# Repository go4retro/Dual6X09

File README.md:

# Dual 6X09E Adapter Schematic and Printed Circuit Board
This PCB will allow the use of two different 6X09E variants in a 6809E-based system.  Only one CPU can be active at any time, and the CPU must be selected before boot.

## Technical Details

The Motorola MC6809E and the Hitachi 63C09E microprocessors both support tristating most of their I/O pins as a way to support a multi-processor environment.  The TSC (Tri State Control) line, when high, places most CPU I/O lines in a high impedence (Hi-Z) state, where they can be safely connected to other output lines.  The address, data, and read/write lines are tristated when TSC is set to logical 1 (5volt). Other lines, like E, Q, the various interrupt lines, and RESET are all inputs, which means they can always be connected together.

This is enough to support running two CPUs in a Tandy Color computer.  However, some aftermarket devices that reside in the CPU socket require access to additional output lines on the CPU that are not tri-stated (LIC, AVMA, BUSY, BA, and BS).  These lines tell the rest of the circuit the internal state of the CPU, so it makes sense they are always active.  Thus, these lines must be tri-stated using external components so the relevant signal from the currently active CPU will be sent to the CPU socket. If these signals are not needed, the external circuitry can be simply omitted.

## Purchase
You can purchase this PCB at http://store.go4retro.com/dual-6x09-pcb/

## License
Copyright (C) 2017-20  Jim Brain, RETRO Innovations

These files are free designs; you can redistribute them and/or modify
them under the terms of the Creative Commons Attribution-ShareAlike 
4.0 International License.

You should have received a copy of the license along with this
work. If not, see <http://creativecommons.org/licenses/by-sa/4.0/>.

These files are distributed in the hope that they will be useful,
but WITHOUT ANY WARRANTY; without even the implied warranty of
MERCHANTABILITY or FITNESS FOR A PARTICULAR PURPOSE.  See the
license for more details.

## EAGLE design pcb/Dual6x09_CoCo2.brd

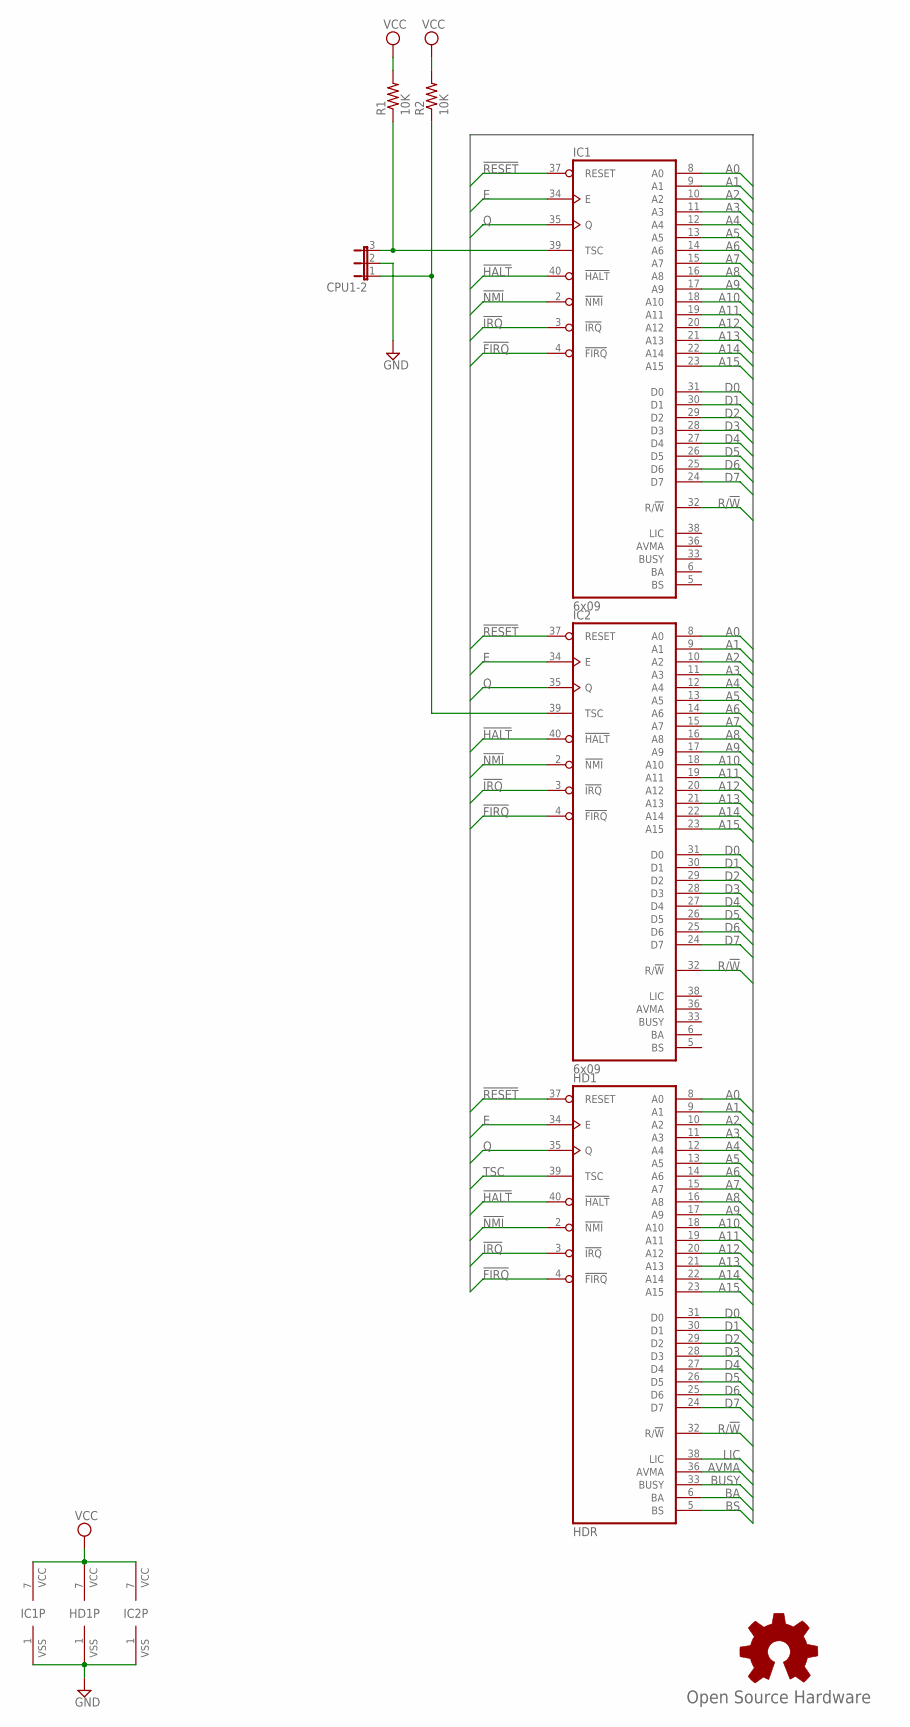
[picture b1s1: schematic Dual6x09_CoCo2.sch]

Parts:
CPU1-2: JP2E; JP2
GOLD_ORB_SM1: Open Source Hardware; OSHW_5MM
HD1: HDR; DIL40-ROUNDPAD
IC1, IC2: 6x09; DIL40-ROUNDPAD
R1, R2: 10K; 0204V

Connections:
!FIRQ: HD1.4 (!FIRQ), IC1.4 (!FIRQ), IC2.4 (!FIRQ)
!HALT: HD1.40 (!HALT), IC1.40 (!HALT), IC2.40 (!HALT)
!IRQ: HD1.3 (!IRQ), IC1.3 (!IRQ), IC2.3 (!IRQ)
!NMI: HD1.2 (!NMI), IC1.2 (!NMI), IC2.2 (!NMI)
!RESET: HD1.37 (RESET), IC1.37 (RESET), IC2.37 (RESET)
A0: HD1.8 (A0), IC1.8 (A0), IC2.8 (A0)
A1: HD1.9 (A1), IC1.9 (A1), IC2.9 (A1)
A2: HD1.10 (A2), IC1.10 (A2), IC2.10 (A2)
A3: HD1.11 (A3), IC1.11 (A3), IC2.11 (A3)
A4: HD1.12 (A4), IC1.12 (A4), IC2.12 (A4)
A5: HD1.13 (A5), IC1.13 (A5), IC2.13 (A5)
A6: HD1.14 (A6), IC1.14 (A6), IC2.14 (A6)
A7: HD1.15 (A7), IC1.15 (A7), IC2.15 (A7)
A8: HD1.16 (A8), IC1.16 (A8), IC2.16 (A8)
A9: HD1.17 (A9), IC1.17 (A9), IC2.17 (A9)
A10: HD1.18 (A10), IC1.18 (A10), IC2.18 (A10)
A11: HD1.19 (A11), IC1.19 (A11), IC2.19 (A11)
A12: HD1.20 (A12), IC1.20 (A12), IC2.20 (A12)
A13: HD1.21 (A13), IC1.21 (A13), IC2.21 (A13)
A14: HD1.22 (A14), IC1.22 (A14), IC2.22 (A14)
A15: HD1.23 (A15), IC1.23 (A15), IC2.23 (A15)
AVMA: HD1.36 (AVMA)
BA: HD1.6 (BA)
BS: HD1.5 (BS)
BUSY: HD1.33 (BUSY)
D0: HD1.31 (D0), IC1.31 (D0), IC2.31 (D0)
D1: HD1.30 (D1), IC1.30 (D1), IC2.30 (D1)
D2: HD1.29 (D2), IC1.29 (D2), IC2.29 (D2)
D3: HD1.28 (D3), IC1.28 (D3), IC2.28 (D3)
D4: HD1.27 (D4), IC1.27 (D4), IC2.27 (D4)
D5: HD1.26 (D5), IC1.26 (D5), IC2.26 (D5)
D6: HD1.25 (D6), IC1.25 (D6), IC2.25 (D6)
D7: HD1.24 (D7), IC1.24 (D7), IC2.24 (D7)
E: HD1.34 (E), IC1.34 (E), IC2.34 (E)
GND: CPU1-2.2, HD1.1 (VSS), IC1.1 (VSS), IC2.1 (VSS)
LIC: HD1.38 (LIC)
unnamed: CPU1-2.1, IC2.39 (TSC), R2.1
unnamed: CPU1-2.3, IC1.39 (TSC), R1.1
Q: HD1.35 (Q), IC1.35 (Q), IC2.35 (Q)
R/!W: HD1.32 (R/!W), IC1.32 (R/!W), IC2.32 (R/!W)
TSC: HD1.39 (TSC)
VCC: HD1.7 (VCC), IC1.7 (VCC), IC2.7 (VCC), R1.2, R2.2

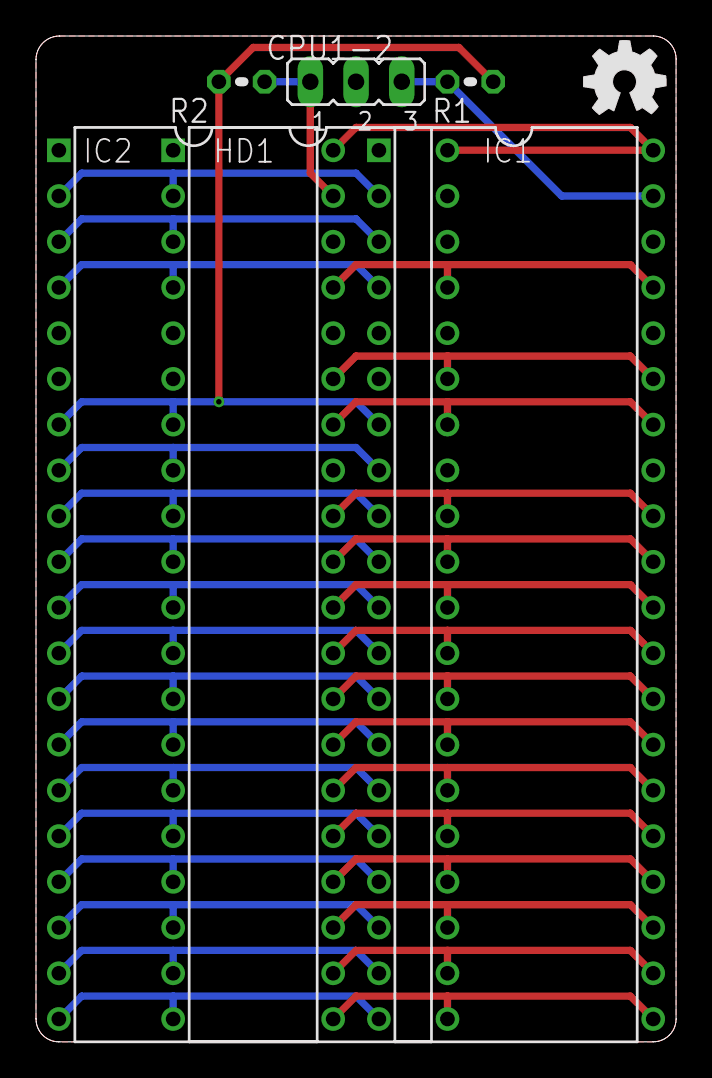
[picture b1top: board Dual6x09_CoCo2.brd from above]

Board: 2 copper layers, 35.6 x 55.9 mm, 7 parts (0 on the bottom side), 36 nets.

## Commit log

2021-01-09 Added DAT/MMU functionality support
2021-01-21 Update technical details
2021-01-21 Add in CoCo 2 'F' board design that should work with the CoCoVGA
